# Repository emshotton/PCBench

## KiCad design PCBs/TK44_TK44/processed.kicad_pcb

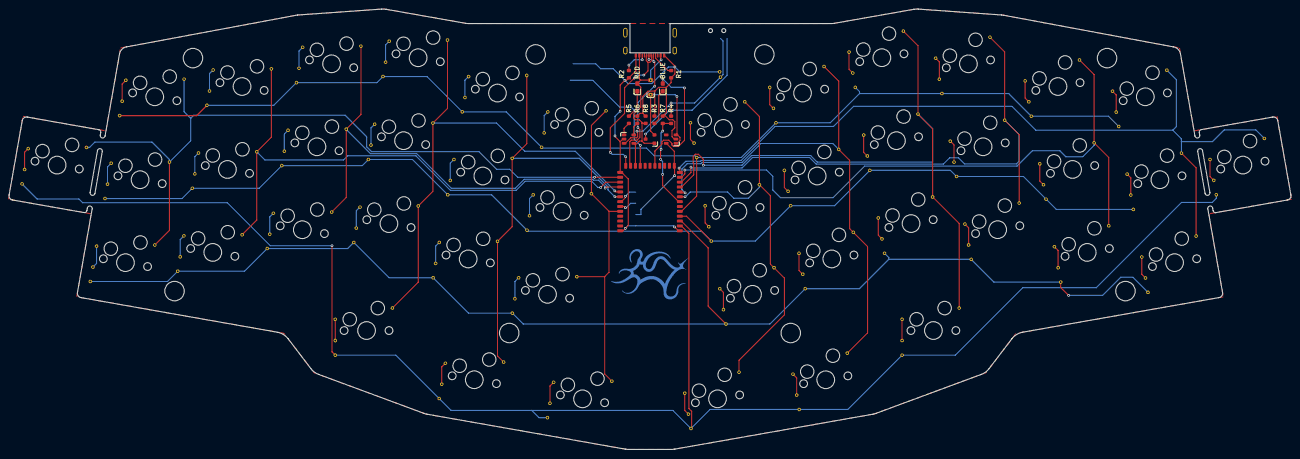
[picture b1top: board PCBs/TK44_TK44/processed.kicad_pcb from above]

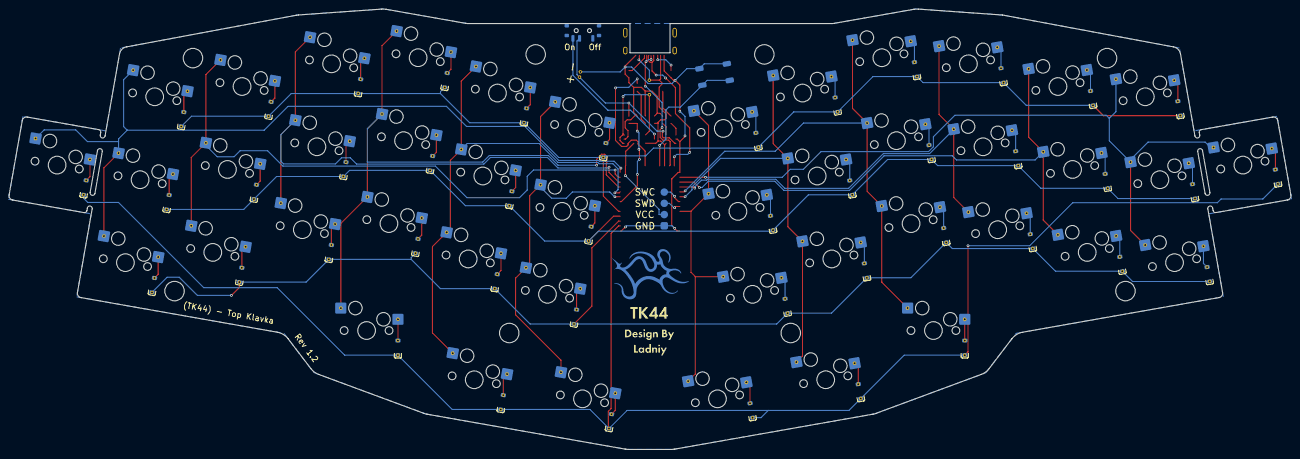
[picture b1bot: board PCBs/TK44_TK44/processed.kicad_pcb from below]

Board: 2 copper layers, 289.9 x 99.6 mm, 117 parts (48 on the bottom side), 79 nets.

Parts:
D1, D2, D3, D4, D5, D6, D7, D8, D9, D10, D11, D12, D13, D14, D15, D16, D17, D18, D19, D20, D21, D22, D23, D24, D25, D26, D27, D28, D29, D30, D31, D32, D33, D34, D35, D36, D37, D38, D39, D40, D41, D42, D43, D44, D46: 1N5819; D_SOD-123
D45: BLUE; LED_0603
D47: RED; LED_0603
H1, H2, H3, H4, H5, H6, H7, H8: Hole_Mount_M4
J1: BATT; Battery_Connector
J2: SWD; Connector_THT_1x4_2.54
J3: USB_C_Receptacle_USB2.0; USB-C-C168688
LOGO1: LOGO; logo
Q1: AO3407; SOT-23
R1, R2: 5.1K; R_0603
R3, R5: 1K; R_0603
R4: 810K; R_0603
R6: 3.3K; R_0603
R7: 2M; R_0603
R8: 100K; R_0603
SW1, SW2, SW3, SW4, SW5, SW6, SW7, SW8, SW9, SW10, SW11, SW12, SW13, SW14, SW15, SW16, SW17, SW18, SW19, SW20, SW21, SW22, SW23, SW24, SW25, SW26, SW27, SW28, SW29, SW30, SW31, SW32, SW33, SW34, SW35, SW36, SW37, SW39, SW42, SW44: MX; Switch_Mx_Hotswap_1u
SW38, SW40, SW41, SW43: MX; Switch_Mx_Hotswap_1.25u
SW45: SW_DPDT; MSK-12C02
SWT1: SW_Push; K2-1187SQ
U1: HOLYIOT-18010; Holyiot-18010-nRF52840
U2: MCP73831; SOT-23-5
U3: XC6220-3.3V; SOT-23-5

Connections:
/BLUE_LED: D45.2 (A), U1.18 (P0.23)
/BT_PIN: R4.2, R7.1, U1.7 (P0.02/AIN0)
/CC1: J3.A5 (CC1), R1.1
/CC2: J3.B5 (CC2), R2.1
/DATA+: J3.A6 (D+), J3.B6 (D+), U1.24 (USB_D+)
/DATA-: J3.A7 (D-), J3.B7 (D-), U1.23 (USB_D-)
/P0.04: SW11.2, SW23.2, SW35.2, U1.12 (P0.04/AIN2)
/P0.05: SW12.2, SW24.2, SW36.2, SW44.2, U1.13 (P0.05/AIN3)
/P0.22: SW1.2, SW13.2, SW25.2, SW37.2, U1.26 (P0.22)
/P0.28: SW7.2, SW19.2, SW31.2, SW41.2, U1.8 (P0.28/AIN4)
/P0.29: SW8.2, SW20.2, SW32.2, SW42.2, U1.9 (P0.29/AIN5)
/P0.30: SW9.2, SW21.2, SW33.2, SW43.2, U1.10 (P0.30/AIN6)
/P0.31: SW10.2, SW22.2, SW34.2, U1.11 (P0.31/AIN7)
/P1.00: SW2.2, SW14.2, SW26.2, U1.27 (P1.00)
/P1.01: SW4.2, SW16.2, SW28.2, SW38.2, U1.29 (P1.01)
/P1.02: SW5.2, SW17.2, SW29.2, SW39.2, U1.30 (P1.02)
/P1.03: SW3.2, SW15.2, SW27.2, U1.28 (P1.03)
/P1.04: SW6.2, SW18.2, SW30.2, SW40.2, U1.33 (P1.04)
/P1.10: D25.1 (K), D26.1 (K), D27.1 (K), D28.1 (K), D29.1 (K), D30.1 (K), D31.1 (K), D32.1 (K), D33.1 (K), D34.1 (K), D35.1 (K), D36.1 (K), U1.3 (P1.10)
/P1.11: D37.1 (K), D38.1 (K), D39.1 (K), D40.1 (K), D41.1 (K), D42.1 (K), D43.1 (K), D44.1 (K), U1.2 (P1.11)
/P1.13: D13.1 (K), D14.1 (K), D15.1 (K), D16.1 (K), D17.1 (K), D18.1 (K), D19.1 (K), D20.1 (K), D21.1 (K), D22.1 (K), D23.1 (K), D24.1 (K), U1.4 (P1.13)
/P1.15: D1.1 (K), D2.1 (K), D3.1 (K), D4.1 (K), D5.1 (K), D6.1 (K), D7.1 (K), D8.1 (K), D9.1 (K), D10.1 (K), D11.1 (K), D12.1 (K), U1.5 (P1.15)
/RESET: SWT1.1, U1.21 (P0.18/RESET)
/SWC: J2.4, U1.31 (SWDCLK)
/SWD: J2.3, U1.32 (SWDIO)
/VBAT: J1.1, R4.1, SW45.2, U2.3 (VBAT)
/VBUS: D46.2 (A), D47.2 (A), J3.A4 (VBUS), Q1.1 (G), R8.1, U1.22 (VBUS), U2.4 (VDD)
/nRF_VDD: J2.2, U1.14 (VDD), U3.5 (VOUT)
GND: J1.2, J2.1, J3.A1 (GND), R1.2, R2.2, R3.2, R6.2, R7.2, R8.2, SWT1.2, U1.1 (GND), U1.25 (GND), U1.37 (GND), U2.2 (VSS), U3.2 (GND)
unnamed: D1.2 (A), SW1.1
unnamed: D2.2 (A), SW2.1
unnamed: D3.2 (A), SW3.1
unnamed: D4.2 (A), SW4.1
unnamed: D5.2 (A), SW5.1
unnamed: D6.2 (A), SW6.1
unnamed: D7.2 (A), SW7.1
unnamed: D8.2 (A), SW8.1
unnamed: D9.2 (A), SW9.1
unnamed: D10.2 (A), SW10.1
unnamed: D11.2 (A), SW11.1
unnamed: D12.2 (A), SW12.1
unnamed: D13.2 (A), SW13.1
unnamed: D14.2 (A), SW14.1
unnamed: D15.2 (A), SW15.1
unnamed: D16.2 (A), SW16.1
unnamed: D17.2 (A), SW17.1
unnamed: D18.2 (A), SW18.1
unnamed: D19.2 (A), SW19.1
unnamed: D20.2 (A), SW20.1
unnamed: D21.2 (A), SW21.1
unnamed: D22.2 (A), SW22.1
unnamed: D23.2 (A), SW23.1
unnamed: D24.2 (A), SW24.1
unnamed: D25.2 (A), SW25.1
unnamed: D26.2 (A), SW26.1
unnamed: D27.2 (A), SW27.1
unnamed: D28.2 (A), SW28.1
unnamed: D29.2 (A), SW29.1
unnamed: D30.2 (A), SW30.1
unnamed: D31.2 (A), SW31.1
unnamed: D32.2 (A), SW32.1
unnamed: D33.2 (A), SW33.1
unnamed: D34.2 (A), SW34.1
unnamed: D35.2 (A), SW35.1
unnamed: D36.2 (A), SW36.1
unnamed: D37.2 (A), SW37.1
unnamed: D38.2 (A), SW38.1
unnamed: D39.2 (A), SW39.1
unnamed: D40.2 (A), SW40.1
unnamed: D41.2 (A), SW41.1
unnamed: D42.2 (A), SW42.1
unnamed: D43.2 (A), SW43.1
unnamed: D44.2 (A), SW44.1
unnamed: D45.1 (K), R3.1
unnamed: D46.1 (K), Q1.2 (S), U3.1 (VIN), U3.3 (EN)
unnamed: D47.1 (K), R5.1
unnamed: Q1.3 (D), SW45.3
unnamed: R5.2, U2.1 (STAT)
unnamed: R6.1, U2.5 (PROG)

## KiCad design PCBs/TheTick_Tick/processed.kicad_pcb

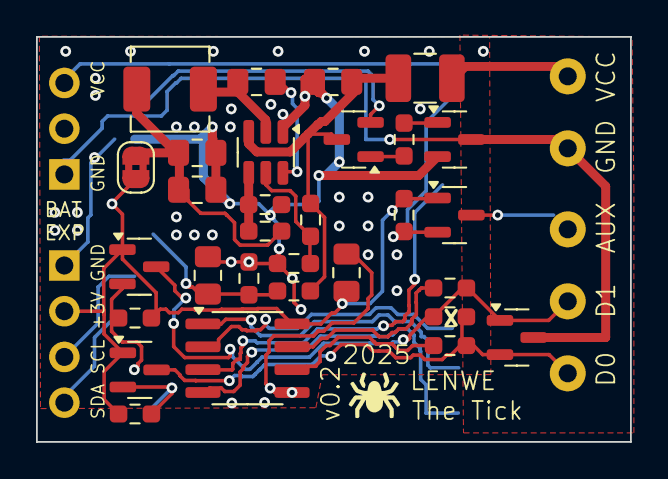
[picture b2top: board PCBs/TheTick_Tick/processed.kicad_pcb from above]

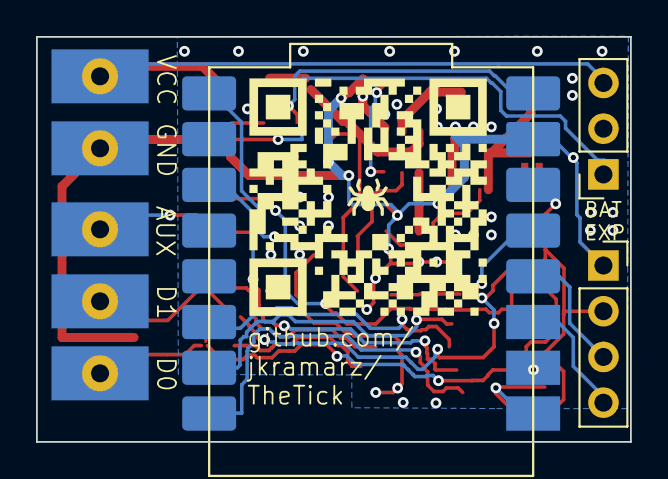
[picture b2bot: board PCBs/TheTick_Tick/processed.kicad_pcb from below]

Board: 2 copper layers, 33.0 x 22.5 mm, 35 parts (5 on the bottom side), 28 nets.

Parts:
C1, C2, C6: 100n; C_0805_2012Metric_Pad1.18x1.45mm_HandSolder
C3, C4, C5: 22u; C_0805_2012Metric_Pad1.18x1.45mm_HandSolder
D2: NUP2105L; SOT-23
D5: BAT54C; SOT-23
F1: 250mA 30V; Fuse_1210_3225Metric_Pad1.42x2.65mm_HandSolder
J1: Conn_01x03; KYOCERA 009176003022006 PTH
J2: Conn_01x02; KYOCERA 009176002022006 PTH
J3: Conn_01x04; PinSocket_1x04_P2.54mm_Vertical
J4: Conn_01x03; PinSocket_1x03_P2.54mm_Vertical
JP7: SolderJumper_2_Bridged; SolderJumper-2_P1.3mm_Bridged2Bar_RoundedPad1.0x1.5mm
L1: 10uH; L_Changjiang_FXL0420
Q1, Q2, Q3, Q4: 2N7002; SOT-23
R1, R8: 22k; R_0603_1608Metric_Pad0.98x0.95mm_HandSolder
R2, R10: 120k; R_0603_1608Metric_Pad0.98x0.95mm_HandSolder
R3, R4, R5, R6, R9: 12k; R_0603_1608Metric_Pad0.98x0.95mm_HandSolder
R7: 100k; R_0603_1608Metric_Pad0.98x0.95mm_HandSolder
R11, R12: 10; R_0603_1608Metric_Pad0.98x0.95mm_HandSolder
R13: 120; R_0603_1608Metric_Pad0.98x0.95mm_HandSolder
U1: TPS54202DDC; SOT-23-6
U2: THVD1410D; SOIC-8_3.9x4.9mm_P1.27mm
U3: ESP32-C3_SUPERMINI; MODULE_ESP32-C3_SUPERMINI_SMD

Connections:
+3.3V: C6.1, J3.2, JP7.2 (B), Q2.1 (G), Q3.1 (G), Q4.1 (G), R4.1, R6.1, R9.1, U2.8 (VCC), U3.3.3 (3V3)
+5V: D5.2, U3.5V
AUX: J1.3, Q3.3 (D)
AUX SENSE: Q3.2 (S), R4.2, U3.5 (GPIO5)
D0: D2.2 (K), J1.1, Q2.3 (D), R11.2, R13.2
D0 SENSE: Q2.2 (S), R9.2, U3.0 (GPIO0)
D1: D2.1 (K), J1.2, Q4.3 (D), R12.2, R13.1
D1 SENSE: Q4.2 (S), R6.2, U3.1 (GPIO1)
GND: C1.2, C3.2, C4.2, C5.2, C6.2, J3.1, Q1.2 (S), R1.2, R3.2, R8.1, U1.1 (GND), U2.5 (GND), U3.G (GND)
GNDPWR: D2.3 (A), J2.1, J4.1, Q1.3 (D)
LCD SCL: J3.3, U3.3 (GPIO3)
LCD SDA: J3.4, U3.2 (GPIO2)
unnamed: D5.1, R5.1
unnamed: C3.1, C4.1, JP7.1 (A), L1.1, R7.1
unnamed: Q1.1 (G), R5.2
unnamed: C2.1, U1.6 (BOOT)
unnamed: R2.1, R8.2, U1.5 (EN)
unnamed: R1.1, R7.2, U1.4 (FB)
unnamed: C2.2, L1.2, U1.2 (SW)
unnamed: C5.1, D5.3, F1.2, R2.2, R10.1, U1.3 (VIN)
unnamed: R11.1, U2.6 (A)
unnamed: R12.1, U2.7 (B)
RS485_DE: U2.3 (DE), U3.7 (GPIO7)
RS485_RE: U2.2 (~RE), U3.10 (GPIO10)
RS485_RX: U2.1 (RO), U3.20 (GPIO20)
RS485_TX: U2.4 (DI), U3.21 (GPIO21)
VDC: F1.1, J2.2, J4.3
V_SENSE: C1.1, R3.1, R10.2, U3.4 (GPIO4)

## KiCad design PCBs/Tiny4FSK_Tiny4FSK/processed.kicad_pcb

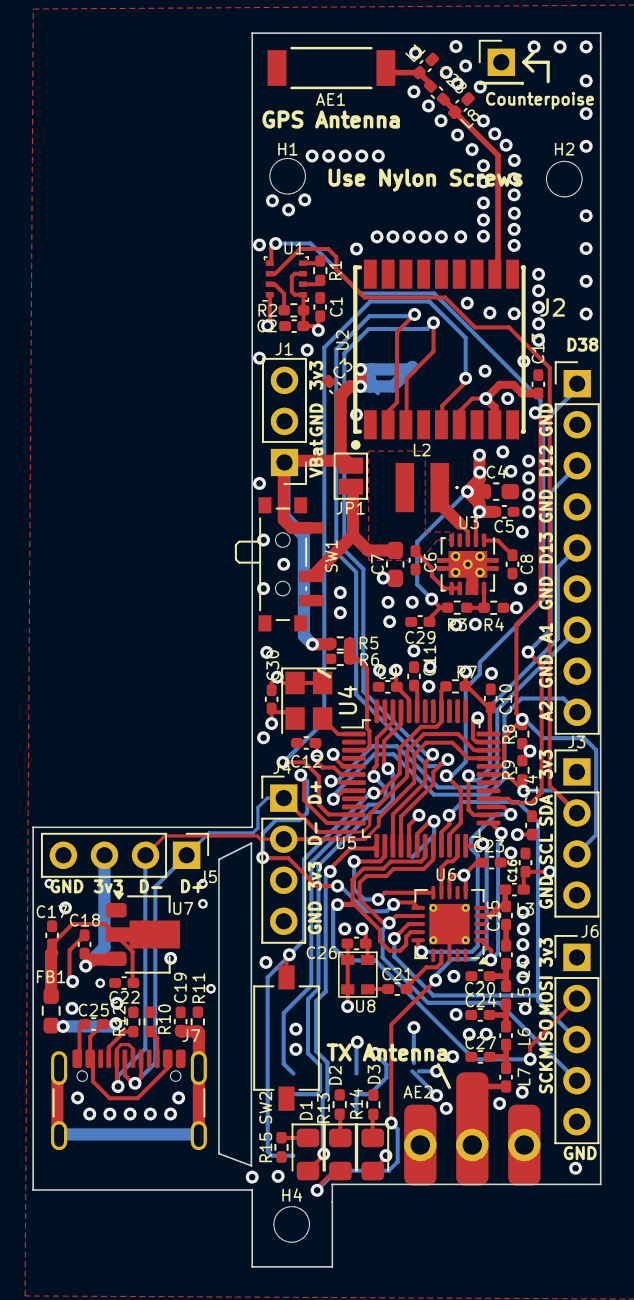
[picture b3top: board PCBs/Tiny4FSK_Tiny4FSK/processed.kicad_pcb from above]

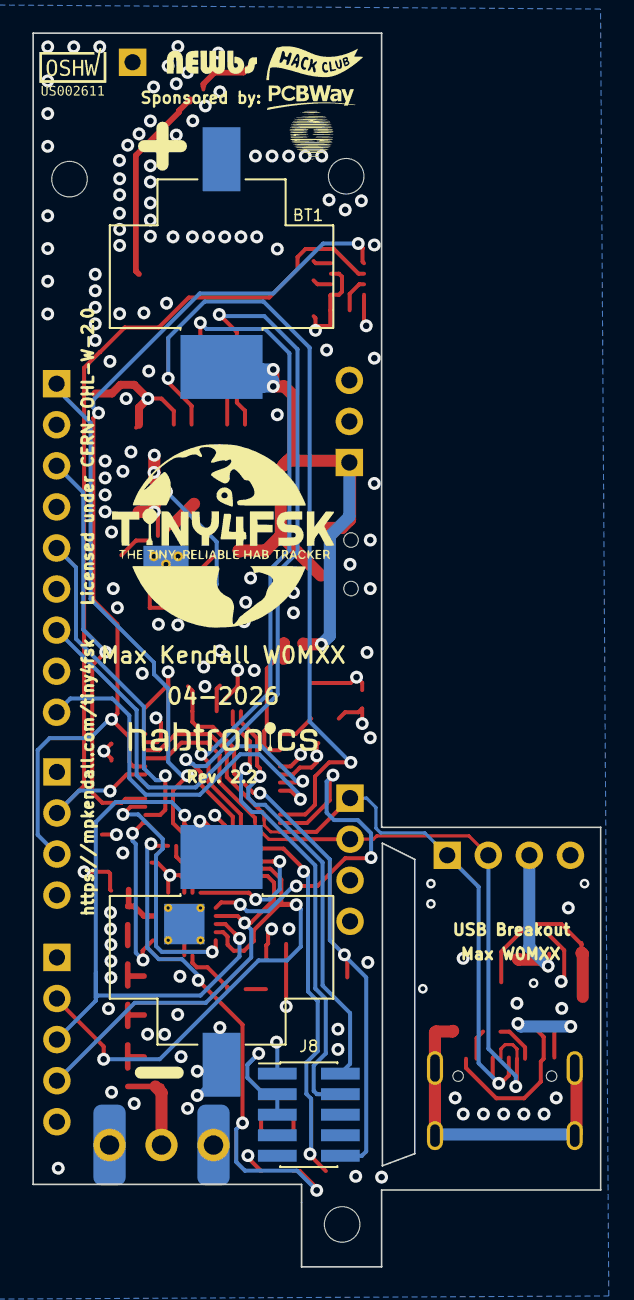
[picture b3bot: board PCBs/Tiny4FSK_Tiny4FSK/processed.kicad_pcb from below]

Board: 4 copper layers, 35.1 x 76.3 mm, 83 parts (2 on the bottom side), 55 nets.

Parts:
AE1: 1575AT43A0040; ANT_1575AT_JOT
AE2: TX Antenna; Antenna_Whip
BT1: BK-53; BAT_53
C1, C14: 10uF; C_0402_1005Metric_Pad0.74x0.62mm_HandSolder
C2, C3, C11, C18, C22: 1uF; C_0402_1005Metric_Pad0.74x0.62mm_HandSolder
C4: 22uF; C_0603_1608Metric_Pad1.08x0.95mm_HandSolder
C5, C8, C9, C13, C16, C23, C29: 100nF; C_0402_1005Metric_Pad0.74x0.62mm_HandSolder
C6, C10, C17, C25, C26, C30: 100 nF; C_0402_1005Metric_Pad0.74x0.62mm_HandSolder
C7: 10 uF; C_0603_1608Metric_Pad1.08x0.95mm_HandSolder
C12: 10 uF; C_0402_1005Metric_Pad0.74x0.62mm_HandSolder
C15: 9.1 pF; C_0402_1005Metric_Pad0.74x0.62mm_HandSolder
C19: 4.7 nF; C_0402_1005Metric_Pad0.74x0.62mm_HandSolder
C20: 8 pF; C_0402_1005Metric_Pad0.74x0.62mm_HandSolder
C21: 100 pF; C_0402_1005Metric_Pad0.74x0.62mm_HandSolder
C24: 6 pF; C_0402_1005Metric_Pad0.74x0.62mm_HandSolder
C27: 5 pF; C_0402_1005Metric_Pad0.74x0.62mm_HandSolder
C28: 2.7pF; C_0402_1005Metric_Pad0.74x0.62mm_HandSolder
D1: Success; LED_0805_2012Metric_Pad1.15x1.40mm_HandSolder
D2: Error; LED_0805_2012Metric_Pad1.15x1.40mm_HandSolder
D3: Power; LED_0805_2012Metric_Pad1.15x1.40mm_HandSolder
FB1: BLM18AG121SN1D; R_0603_1608Metric_Pad0.98x0.95mm_HandSolder
H1, H2, H4: MountingHole; MountingHole_2.2mm_M2
J1: Power Ext; PinHeader_1x03_P2.54mm_Vertical
J2: GPIO; PinHeader_1x09_P2.54mm_Vertical
J3: I2C; PinHeader_1x04_P2.54mm_Vertical
J4: USB; PinHeader_1x04_P2.54mm_Vertical
J5: USB Breakout; PinHeader_1x04_P2.54mm_Vertical
J6: SPI; PinHeader_1x05_P2.54mm_Vertical
J7: USBC; USB_C_Receptacle_GCT_USB4105-xx-A_16P_TopMnt_Horizontal
J8: SWD; PinHeader_2x05_P1.27mm_Vertical_SMD
J9: Counterpoise; PinHeader_1x01_P2.54mm_Vertical
JP1: Switch EN; SolderJumper-2_P1.3mm_Open_Pad1.0x1.5mm
L1, L8: 3.9 nH; L_0402_1005Metric_Pad0.77x0.64mm_HandSolder
L2: 2.2uH; LPS3015222MRB
L3: 220 nH; L_0402_1005Metric_Pad0.77x0.64mm_HandSolder
L4, L5, L6, L7: 14 nH; L_0402_1005Metric_Pad0.77x0.64mm_HandSolder
R1, R2: 10k; R_0402_1005Metric_Pad0.72x0.64mm_HandSolder
R3, R5, R6, R11: 1M; R_0402_1005Metric_Pad0.72x0.64mm_HandSolder
R4: 180k; R_0402_1005Metric_Pad0.72x0.64mm_HandSolder
R7: 220; R_0402_1005Metric_Pad0.72x0.64mm_HandSolder
R8, R9: 1.8k; R_0402_1005Metric_Pad0.72x0.64mm_HandSolder
R10, R12: 5k1; R_0402_1005Metric_Pad0.72x0.64mm_HandSolder
R13, R14, R15: 330; R_0402_1005Metric_Pad0.72x0.64mm_HandSolder
SW1: Power Switch; SW_SPDT_PCM12
SW2: RST; SW_Tactile_SPST_NO_Straight_CK_PTS636Sx25SMTRLFS
U1: BME280; Bosch_LGA-8_2.5x2.5mm_P0.65mm_ClockwisePinNumbering
U2: ATGM336H
U3: TPS61200DRC; Texas_S-PVSON-N10_ThermalVias
U4: ECS-327TXO-2012; Crystal_SMD_3225-4Pin_3.2x2.5mm
U5: ATSAMD21G18A-A; TQFP-48_7x7mm_P0.5mm
U6: SI4063; QFN-20-1EP_4x4mm_P0.5mm_EP2.5x2.5mm_ThermalVias
U7: Linear Step-Down; MCP1700
U8: ECS-TXO-20CSMV4

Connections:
+3.3V: C1.2, C2.1, C4.1, C5.1, C9.2, C10.1, C12.1, C13.2, C14.1, C16.2, C18.1, C23.1, C26.2, C29.1, C30.2, D3.2 (A), J1.3, J3.1, J4.3, J5.3, J6.1, J8.1, L3.1, R2.1, R3.1, R7.2, R8.1, R9.2, U1.6 (VDDIO), U1.8 (VDD), U2.6 (VBAT), U2.8 (VCC), U3.2 (VOUT), U4.1 (EN), U4.4 (VDD), U5.6 (VDDANA), U5.17 (VDDIO), U5.36 (VDDIO), U5.44 (VDDIN), U6.6 (VDD_1), U6.8 (VDD_2), U7.2 (VO), U8.4 (VDD)
+BATT: BT1.1 (+), C3.1, J1.1, JP1.2 (B), R5.1, SW1.1 (A)
A1: J2.7, U5.7 (PB08)
A2: J2.9, U5.8 (PB09)
ANT_GPS: C28.1, L8.2, U2.11 (RF_IN)
BATT_SENSE: R5.2, R6.1, U5.3 (PA02)
BST_IN: C6.1, C7.1, JP1.1 (A), L2.2, SW1.2 (B), U3.5 (VIN), U3.6 (EN), U3.7 (UVLO)
D12: J2.3, U5.28 (PA19)
D13: J2.5, U5.26 (PA17)
D38: J2.1, U5.22 (PA13)
D+: J4.1, J5.1, J7.A6 (D+), J7.B6 (D+), U5.34 (PA25)
D-: J4.2, J5.2, J7.A7 (D-), J7.B7 (D-), U5.33 (PA24)
ERROR: D2.2 (A), U5.24 (PA15)
Earth: AE2.2 (Shield), BT1.2 (-), C1.1, C2.2, C3.2, C4.2, C5.2, C6.2, C7.2, C8.2, C9.1, C10.2, C11.2, C12.2, C13.1, C14.2, C16.1, C17.2, C18.2, C19.1, C20.2, C22.1, C23.2, C24.2, C25.2, C26.1, C27.2, C29.2, C30.1, J1.2, J2.2, J2.4, J2.6, J2.8, J3.4, J4.4, J5.4, J6.5, J7.A1 (GND), J7.A12 (GND), J7.B1 (GND), J7.B12 (GND), J8.3, J8.5, J9.1 (Pin_1_1), L1.1, L8.1, R1.2, R4.2, R6.2, R10.1, R11.2, R12.1, R13.2, R14.2, R15.2, SW2.1, U1.1 (GND), U1.7 (GND), U2.1 (GND), U2.10 (GND), U2.12 (GND), U3.4 (PGND), U3.8 (PS), U3.9 (GND), U3.11 (PAD), U4.2 (GND), U5.5 (GNDANA), U5.18 (GND), U5.35 (GND), U5.42 (GND), U6.18 (GND_1), U6.21 (GND_2), U7.1 (GND), U8.1 (GND), U8.2 (GND)
GPIO0: U5.23 (PA14), U6.9 (GPIO0)
GPIO1: U5.14 (PA09), U6.10 (GPIO1)
GPS_EN: U2.5 (ONOFF), U5.11 (PA06)
LIN: C17.1, C22.2, FB1.2, U7.3 (VI)
MISO: J6.3, U5.21 (PA12), U6.13 (SDO)
MOSI: J6.2, U5.19 (PB10), U6.14 (SDI)
unnamed: AE1.1 (A_1), C28.2, L1.2
unnamed: AE2.1 (RF), L7.2
unnamed: C15.2, L4.1
unnamed: C20.1, L4.2, L5.1
unnamed: C24.1, L5.2, L6.1
unnamed: C27.1, L6.2, L7.1
unnamed: D1.1 (K), R15.1
unnamed: D2.1 (K), R13.1
unnamed: D3.1 (K), R14.1
unnamed: J7.A5 (CC1), R12.2
unnamed: J7.B5 (CC2), R10.2
unnamed: C19.2, J7.S1 (SHIELD), R11.1
unnamed: R2.2, U1.2 (CSB)
unnamed: R1.1, U1.5 (SDO)
unnamed: R3.2, R4.1, U3.10 (FB)
unnamed: L2.1, U3.3 (L)
unnamed: C8.1, U3.1 (VAUX)
unnamed: C11.1, U5.43 (VDDCORE)
unnamed: C21.2, U6.17 (XIN)
RF_ANT: C15.1, L3.2, U6.4 (TX)
RF_RST: U5.12 (PA07), U6.11 (NIRQ)
RF_SS: U5.27 (PA18), U6.15 (NSEL)
RF_XO: C21.1, U8.3 (CLK_OUT)
RXD: U2.2 (TXD), U5.16 (PA11)
SCK: J6.4, U5.20 (PB11), U6.12 (SCLK)
SCL: J3.3, R8.2, U1.4 (SCK), U5.32 (PA23)
SDA: J3.2, R9.1, U1.3 (SDI), U5.31 (PA22)
SDN: U5.25 (PA16), U6.1 (SDN)
SUCCESS: D1.2 (A), U5.13 (PA08)
SWCLK: J8.4, U5.45 (PA30)
SWDIO: J8.2, U5.46 (PA31)
TCXO: U4.3 (OUTPUT), U5.1 (PA00)
TXD: U2.3 (RXD), U5.15 (PA10)
USB: C25.1, FB1.1, J7.A4 (VBUS), J7.A9 (VBUS), J7.B4 (VBUS), J7.B9 (VBUS)
nRST: J8.10, R7.1, SW2.2, U5.40 (~RESET)

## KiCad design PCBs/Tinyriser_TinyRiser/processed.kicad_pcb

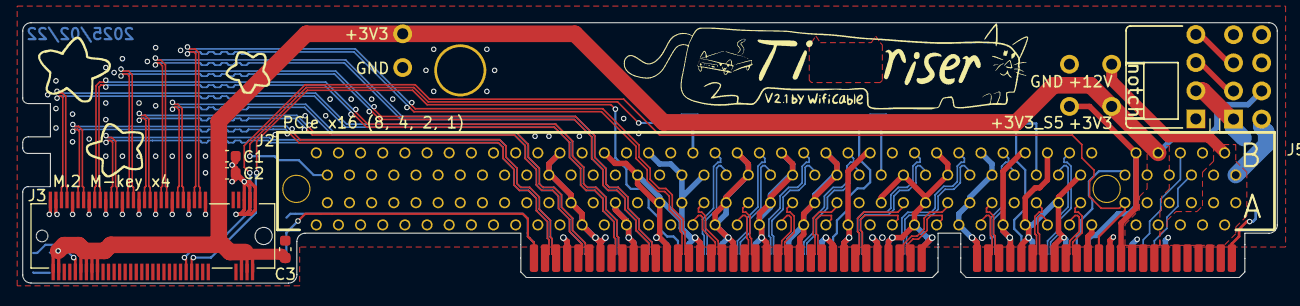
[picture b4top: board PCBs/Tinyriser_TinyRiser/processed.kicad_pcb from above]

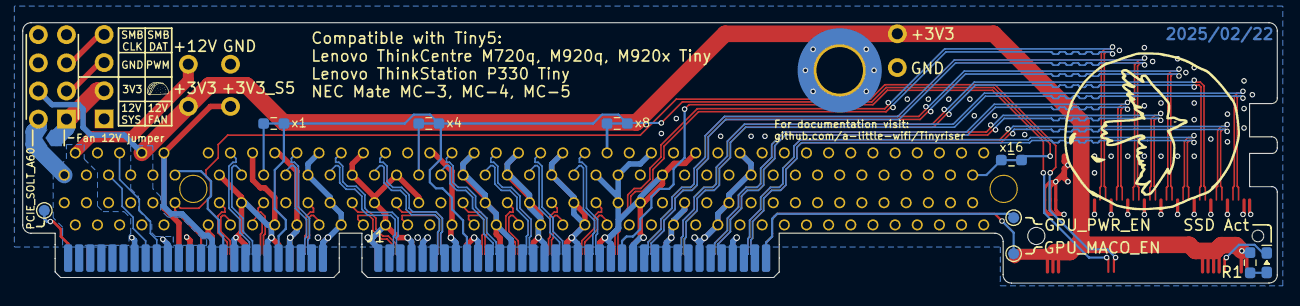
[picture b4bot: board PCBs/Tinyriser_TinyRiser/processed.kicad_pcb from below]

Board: 4 copper layers, 113.2 x 23.5 mm, 25 parts (12 on the bottom side), 70 nets.

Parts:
C1, C3: 10uF; C_0603_1608Metric
C2: 100nF; C_0603_1608Metric
D1: LED; D_0603_1608Metric_Pad1.05x0.95mm_HandSolder
H1: MountingHole_Pad; MountingHole_4.3mm_M4_ISO7380_Pad_TopOnly
J1: TinyRiser
J2: Bus_PCI_Express_x16; PCIe_x16_tht
J3: Bus_M.2_Socket_M; M.2_NGFF_KeyM_H5.3_Vertical
J5: Conn_02x04_Odd_Even; PinSocket_2x04_P2.54mm_Horizontal
JP1: SolderJumper_2_Open; SolderJumper-2_P1.3mm_Open_TrianglePad1.0x1.5mm
M1: Fan_4pin; PinHeader_1x04_P2.54mm_Horizontal
R1: 5K1; R_0603_1608Metric_Pad0.98x0.95mm_HandSolder
R3, R4, R5, R6: 0R; R_0603_1608Metric_Pad0.98x0.95mm_HandSolder
TP1: PCIE_SOLT_A60; TestPoint_Pad_D1.0mm
TP2: GPU_MACO_EN; TestPoint_Pad_D1.0mm
TP3: GPU_PWR_EN; TestPoint_Pad_D1.0mm
TP4, TP8: +3V3; TestPoint_THTPad_D1.5mm_Drill0.7mm
TP5: +3V3_S5; TestPoint_THTPad_D1.5mm_Drill0.7mm
TP6, TP7: GND; TestPoint_THTPad_D1.5mm_Drill0.7mm
TP9: +12V; TestPoint_THTPad_D1.5mm_Drill0.7mm

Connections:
+3V3: C1.1, C2.1, C3.1, J1.A51 (+3V3), J1.A52 (+3V3), J1.A53 (+3V3), J1.B48 (+3V3), J1.B49 (+3V3), J1.B50 (+3V3), J2.A9 (+3.3V), J2.A10 (+3.3V), J2.B8 (+3.3V), J3.2 (3.3V), J3.4 (3.3V), J3.12 (3.3V), J3.14 (3.3V), J3.16 (3.3V), J3.18 (3.3V), J3.70 (3.3V), J3.72 (3.3V), J3.74 (3.3V), J5.4, R1.2, TP4.1, TP8.1
+3V3_S5: J1.A50 (+3V3_S5), J1.B47 (+3V3_S5), J2.B10 (3.3Vaux), TP5.1
+12V: J1.A54 (+12V), J1.A55 (+12V), J1.A56 (+12V), J1.A57 (+12V), J1.A58 (+12V), J1.A59 (+12V), J1.B55 (+12V), J1.B56 (+12V), J1.B57 (+12V), J1.B58 (+12V), J1.B59 (+12V), J1.B60 (+12V), J2.A2 (+12V), J2.A3 (+12V), J2.B1 (+12V), J2.B2 (+12V), J2.B3 (+12V), J5.2, JP1.2 (B), TP9.1
+12V_fan: J5.1, JP1.1 (A), M1.2 (+)
GND: C1.2, C2.2, C3.2, H1.1, J1.A4 (GND), J1.A7 (GND), J1.A10 (GND), J1.A13 (GND), J1.A16 (GND), J1.A19 (GND), J1.A22 (GND), J1.A25 (GND), J1.A28 (GND), J1.A29 (GND), J1.A32 (GND), J1.A33 (GND), J1.A36 (GND), J1.A37 (GND), J1.A40 (GND), J1.A41 (GND), J1.A44 (GND), J1.A47 (GND), J1.A49 (GND), J1.B4 (GND), J1.B7 (GND), J1.B10 (GND), J1.B13 (GND), J1.B15 (GND), J1.B18 (GND), J1.B21 (GND), J1.B24 (GND), J1.B27 (GND), J1.B29 (GND), J1.B32 (GND), J1.B33 (GND), J1.B36 (GND), J1.B37 (GND), J1.B40 (GND), J1.B42 (GND), J1.B45 (GND), J1.B51 (GND), J1.B54 (GND), J2.A1 (~PRSNT1), J2.A4 (GND), J2.A12 (GND), J2.A15 (GND), J2.A18 (GND), J2.A20 (GND), J2.A23 (GND), J2.A24 (GND), J2.A27 (GND), J2.A28 (GND), J2.A31 (GND), J2.A34 (GND), J2.A37 (GND), J2.A38 (GND), J2.A41 (GND), J2.A42 (GND), J2.A45 (GND), J2.A46 (GND), J2.A49 (GND), J2.A51 (GND), J2.A54 (GND), J2.A55 (GND), J2.A58 (GND), J2.A59 (GND), J2.A62 (GND), J2.A63 (GND), J2.A66 (GND), J2.A67 (GND), J2.A70 (GND), J2.A71 (GND), J2.A74 (GND), J2.A75 (GND), J2.A78 (GND), J2.A79 (GND), J2.A82 (GND), J2.B4 (GND), J2.B7 (GND), J2.B13 (GND), J2.B16 (GND), J2.B18 (GND), J2.B21 (GND), J2.B22 (GND), J2.B25 (GND), J2.B26 (GND), J2.B29 (GND), J2.B32 (GND), J2.B35 (GND), J2.B36 (GND), J2.B39 (GND), J2.B40 (GND), J2.B43 (GND), J2.B44 (GND), J2.B47 (GND), J2.B49 (GND), J2.B52 (GND), J2.B53 (GND), J2.B56 (GND), J2.B57 (GND), J2.B60 (GND), J2.B61 (GND), J2.B64 (GND), J2.B65 (GND), J2.B68 (GND), J2.B69 (GND), J2.B72 (GND), J2.B73 (GND), J2.B76 (GND), J2.B77 (GND), J2.B80 (GND), J3.1 (GND), J3.3 (GND), J3.9 (GND), J3.15 (GND), J3.21 (GND), J3.27 (GND), J3.33 (GND), J3.39 (GND), J3.45 (GND), J3.51 (GND), J3.57 (GND), J3.71 (GND), J3.73 (GND), J3.75 (GND), J5.6, M1.1 (-), TP6.1, TP7.1
unnamed: D1.2 (A), R1.1
unnamed: D1.1 (K), J3.10 (DAS/~DSS/~LED1)
unnamed: J1.A1 (GPU_MACO_EN), TP2.1
unnamed: J1.B1 (GPU_PWR_EN), TP3.1
unnamed: J1.A60 (PCIE_SOLT_A60), TP1.1
PCIe_CPU_CLKREQ#: J1.B28 (PCIe_CPU_CLKREQ#), J1.B41 (PCIe_CPU_CLKREQ#), J2.B17 (~PRSNT2), J2.B31 (~PRSNT2), J2.B48 (~PRSNT2), J2.B81 (~PRSNT2), R3.1, R3.2, R4.1, R4.2, R5.1, R5.2, R6.1, R6.2
PCIe_CPU_REFCLK+: J1.A46 (PCIe_CPU_REFCLK+), J2.A13 (REFCLK+)
PCIe_CPU_REFCLK-: J1.A45 (PCIe_CPU_REFCLK-), J2.A14 (REFCLK-)
PCIe_CPU_Rx0+: J1.A43 (PCIe_CPU_Rx0+), J2.A16 (PERp0)
PCIe_CPU_Rx0-: J1.A42 (PCIe_CPU_Rx0-), J2.A17 (PERn0)
PCIe_CPU_Rx1+: J1.A39 (PCIe_CPU_Rx1+), J2.A21 (PERp1)
PCIe_CPU_Rx1-: J1.A38 (PCIe_CPU_Rx1-), J2.A22 (PERn1)
PCIe_CPU_Rx2+: J1.A34 (PCIe_CPU_Rx2+), J2.A25 (PERp2)
PCIe_CPU_Rx2-: J1.A35 (PCIe_CPU_Rx2-), J2.A26 (PERn2)
PCIe_CPU_Rx3+: J1.A30 (PCIe_CPU_Rx3+), J2.A29 (PERp3)
PCIe_CPU_Rx3-: J1.A31 (PCIe_CPU_Rx3-), J2.A30 (PERn3)
PCIe_CPU_Rx4+: J1.A26 (PCIe_CPU_Rx4+), J2.A35 (PERp4)
PCIe_CPU_Rx4-: J1.A27 (PCIe_CPU_Rx4-), J2.A36 (PERn4)
PCIe_CPU_Rx5+: J1.A24 (PCIe_CPU_Rx5+), J2.A39 (PERp5)
PCIe_CPU_Rx5-: J1.A23 (PCIe_CPU_Rx5-), J2.A40 (PERn5)
PCIe_CPU_Rx6+: J1.A21 (PCIe_CPU_Rx6+), J2.A43 (PERp6)
PCIe_CPU_Rx6-: J1.A20 (PCIe_CPU_Rx6-), J2.A44 (PERn6)
PCIe_CPU_Rx7+: J1.A18 (PCIe_CPU_Rx7+), J2.A47 (PERp7)
PCIe_CPU_Rx7-: J1.A17 (PCIe_CPU_Rx7-), J2.A48 (PERn7)
PCIe_CPU_Tx0+: J1.B44 (PCIe_CPU_Tx0+), J2.B14 (PETp0)
PCIe_CPU_Tx0-: J1.B43 (PCIe_CPU_Tx0-), J2.B15 (PETn0)
PCIe_CPU_Tx1+: J1.B39 (PCIe_CPU_Tx1+), J2.B19 (PETp1)
PCIe_CPU_Tx1-: J1.B38 (PCIe_CPU_Tx1-), J2.B20 (PETn1)
PCIe_CPU_Tx2+: J1.B35 (PCIe_CPU_Tx2+), J2.B23 (PETp2)
PCIe_CPU_Tx2-: J1.B34 (PCIe_CPU_Tx2-), J2.B24 (PETn2)
PCIe_CPU_Tx3+: J1.B31 (PCIe_CPU_Tx3+), J2.B27 (PETp3)
PCIe_CPU_Tx3-: J1.B30 (PCIe_CPU_Tx3-), J2.B28 (PETn3)
PCIe_CPU_Tx4+: J1.B26 (PCIe_CPU_Tx4+), J2.B33 (PETp4)
PCIe_CPU_Tx4-: J1.B25 (PCIe_CPU_Tx4-), J2.B34 (PETn4)
PCIe_CPU_Tx5+: J1.B23 (PCIe_CPU_Tx5+), J2.B37 (PETp5)
PCIe_CPU_Tx5-: J1.B22 (PCIe_CPU_Tx5-), J2.B38 (PETn5)
PCIe_CPU_Tx6+: J1.B20 (PCIe_CPU_Tx6+), J2.B41 (PETp6)
PCIe_CPU_Tx6-: J1.B19 (PCIe_CPU_Tx6-), J2.B42 (PETn6)
PCIe_CPU_Tx7+: J1.B17 (PCIe_CPU_Tx7+), J2.B45 (PETp7)
PCIe_CPU_Tx7-: J1.B16 (PCIe_CPU_Tx7-), J2.B46 (PETn7)
PCIe_PCH_CLKREQ#: J1.B14 (PCIe_PCH_CLKREQ#), J3.52 (~CLKREQ)
PCIe_PCH_REFCLK+: J1.A15 (PCIe_PCH_REFCLK+), J3.55 (REFCLKp)
PCIe_PCH_REFCLK-: J1.A14 (PCIe_PCH_REFCLK-), J3.53 (REFCLKn)
PCIe_PCH_Rx0+: J1.B12 (PCIe_PCH_Rx0+), J3.43 (PERp0/SATA-B-)
PCIe_PCH_Rx0-: J1.B11 (PCIe_PCH_Rx0-), J3.41 (PERn0/SATA-B+)
PCIe_PCH_Rx1+: J1.A12 (PCIe_PCH_Rx1+), J3.31 (PERp1)
PCIe_PCH_Rx1-: J1.A11 (PCIe_PCH_Rx1-), J3.29 (PERn1)
PCIe_PCH_Rx2+: J1.A8 (PCIe_PCH_Rx2+), J3.19 (PERp2)
PCIe_PCH_Rx2-: J1.A9 (PCIe_PCH_Rx2-), J3.17 (PERn2)
PCIe_PCH_Rx3+: J1.B9 (PCIe_PCH_Rx3+), J3.7 (PERp3)
PCIe_PCH_Rx3-: J1.B8 (PCIe_PCH_Rx3-), J3.5 (PERn3)
PCIe_PCH_Tx0+: J1.B6 (PCIe_PCH_Tx0+), J3.49 (PETp0/SATA-A+)
PCIe_PCH_Tx0-: J1.B5 (PCIe_PCH_Tx0-), J3.47 (PETn0/SATA-A-)
PCIe_PCH_Tx1+: J1.A6 (PCIe_PCH_Tx1+), J3.37 (PETp1)
PCIe_PCH_Tx1-: J1.A5 (PCIe_PCH_Tx1-), J3.35 (PETn1)
PCIe_PCH_Tx2+: J1.B3 (PCIe_PCH_Tx2+), J3.25 (PETp2)
PCIe_PCH_Tx2-: J1.B2 (PCIe_PCH_Tx2-), J3.23 (PETn2)
PCIe_PCH_Tx3+: J1.A3 (PCIe_PCH_Tx3+), J3.13 (PETp3)
PCIe_PCH_Tx3-: J1.A2 (PCIe_PCH_Tx3-), J3.11 (PETn3)
PERST#: J1.A48 (PCIe_RST#), J2.A11 (~PERST), J3.50 (~PERST)
PWM_fan: J5.5, M1.4 (PWM)
SMBCLK: J1.B53 (SMBCLK), J2.B5 (SMCLK), J5.8
SMBDATA: J1.B52 (SMBDATA), J2.B6 (SMDAT), J5.7
Taco_fan: J5.3, M1.3 (Tacho)
WAKE#: J1.B46 (WAKE#), J2.B11 (~WAKE)

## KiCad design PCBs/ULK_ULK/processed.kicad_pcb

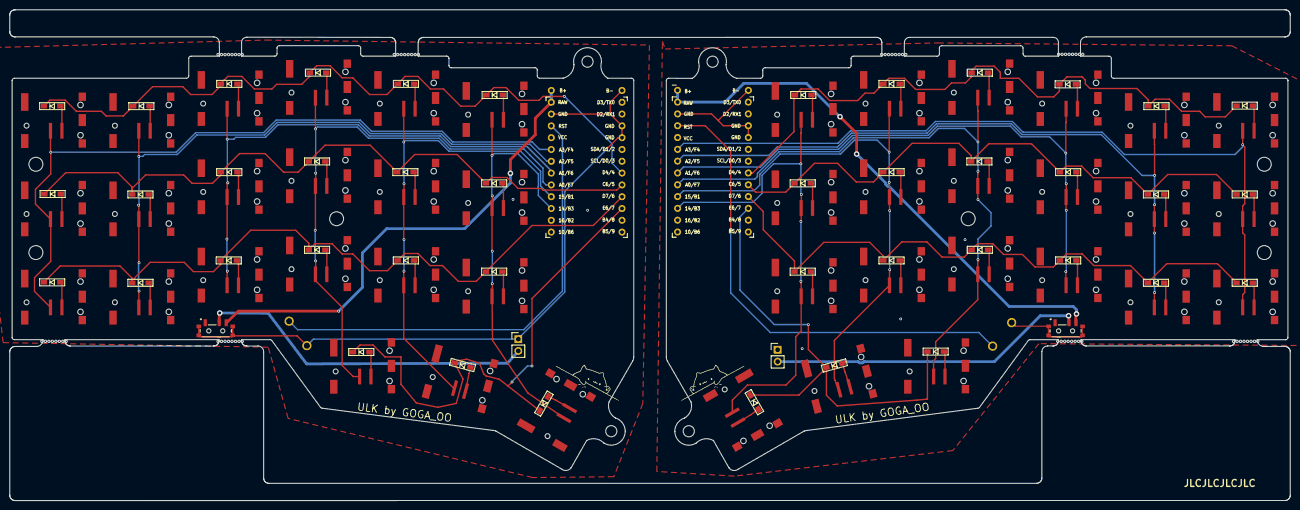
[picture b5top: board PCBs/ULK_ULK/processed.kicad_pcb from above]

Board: 2 copper layers, 275.5 x 105.6 mm, 100 parts (0 on the bottom side), 70 nets.

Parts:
D1, D2, D3, D4, D5, D6, D7, D8, D9, D10, D11, D12, D13, D14, D15, D16, D17, D18, D19, D20, D21, D22, D23, D24, D25, D26, D27, D28, D29, D30, D31, D32, D33, D34, D35, D36, D37, D38, D39, D40, D41, D42: D; D3_SMD_v2
RSW1, RSW2: SW_RESET; ResetSW_1side
SW1, SW2, SW3, SW4, SW5, SW6, SW7, SW8, SW9, SW10, SW11, SW12, SW13, SW14, SW15, SW16, SW17, SW18, SW19, SW20, SW21, SW22, SW23, SW24, SW25, SW26, SW27, SW28, SW29, SW30, SW31, SW32, SW33, SW34, SW35, SW36, SW37, SW38, SW39, SW40, SW41, SW42: SW_PUSH; Cherry_ULP_SMD
SW43, SW44: PCM12SMTR; SW_PCM12SMTR
U1, U2: ProMicro; ProMicro_v3
U3, U5: PinHeader_1x02_P2.54mm_Vertical
mouse-bite-2mm-slot, mouse-bite-2mm-slot#2, mouse-bite-2mm-slot#3, mouse-bite-2mm-slot#4, mouse-bite-2mm-slot#5, mouse-bite-2mm-slot#6, mouse-bite-2mm-slot#7, mouse-bite-2mm-slot#8: VAL**; mouse-bite-2mm-slot

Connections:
1V5: SW44.3, U2.24 (RAW)
+1V5: SW43.3, U1.24 (RAW)
GND: RSW1.2, SW1.3 (G), SW2.3 (G), SW3.3 (G), SW4.3 (G), SW5.3 (G), SW6.3 (G), SW7.3 (G), SW8.3 (G), SW9.3 (G), SW10.3 (G), SW11.3 (G), SW12.3 (G), SW13.3 (G), SW14.3 (G), SW15.3 (G), SW16.3 (G), SW17.3 (G), SW18.3 (G), SW19.3 (G), SW20.3 (G), SW21.3 (G), SW43.S1 (SHIELD), SW43.S2 (SHIELD), SW43.S3 (SHIELD), SW43.S4 (SHIELD), U1.3 (GND), U1.4 (GND), U1.23 (GND), U3.1 (-)
GNDA: RSW2.2, SW22.3 (G), SW23.3 (G), SW24.3 (G), SW25.3 (G), SW26.3 (G), SW27.3 (G), SW28.3 (G), SW29.3 (G), SW30.3 (G), SW31.3 (G), SW32.3 (G), SW33.3 (G), SW34.3 (G), SW35.3 (G), SW36.3 (G), SW37.3 (G), SW38.3 (G), SW39.3 (G), SW40.3 (G), SW41.3 (G), SW42.3 (G), SW44.S1 (SHIELD), SW44.S2 (SHIELD), SW44.S3 (SHIELD), SW44.S4 (SHIELD), U2.3 (GND), U2.4 (GND), U2.23 (GND), U5.1 (-)
unnamed: D1.2 (A), SW1.2
unnamed: D2.2 (A), SW2.2
unnamed: D3.2 (A), SW3.2
unnamed: D4.2 (A), SW4.2
unnamed: D5.2 (A), SW5.2
unnamed: D6.2 (A), SW6.2
unnamed: D7.2 (A), SW7.2
unnamed: D8.2 (A), SW8.2
unnamed: D9.2 (A), SW9.2
unnamed: D10.2 (A), SW10.2
unnamed: D11.2 (A), SW11.2
unnamed: D12.2 (A), SW12.2
unnamed: D13.2 (A), SW13.2
unnamed: D14.2 (A), SW14.2
unnamed: D15.2 (A), SW15.2
unnamed: D16.2 (A), SW16.2
unnamed: D17.2 (A), SW17.2
unnamed: D18.2 (A), SW18.2
unnamed: D19.2 (A), SW19.2
unnamed: D20.2 (A), SW20.2
unnamed: D21.2 (A), SW21.2
unnamed: D22.2 (A), SW22.2
unnamed: D23.2 (A), SW23.2
unnamed: D24.2 (A), SW24.2
unnamed: D25.2 (A), SW25.2
unnamed: D26.2 (A), SW26.2
unnamed: D27.2 (A), SW27.2
unnamed: D28.2 (A), SW28.2
unnamed: D29.2 (A), SW29.2
unnamed: D30.2 (A), SW30.2
unnamed: D31.2 (A), SW31.2
unnamed: D32.2 (A), SW32.2
unnamed: D33.2 (A), SW33.2
unnamed: D34.2 (A), SW34.2
unnamed: D35.2 (A), SW35.2
unnamed: D36.2 (A), SW36.2
unnamed: D37.2 (A), SW37.2
unnamed: D38.2 (A), SW38.2
unnamed: D39.2 (A), SW39.2
unnamed: D40.2 (A), SW40.2
unnamed: D41.2 (A), SW41.2
unnamed: D42.2 (A), SW42.2
unnamed: SW43.2, U3.2 (+)
unnamed: SW44.2, U5.2 (+)
col0: SW1.1, SW7.1, SW13.1, U1.20 (F4/A3)
col0_r: SW22.1, SW28.1, SW34.1, U2.20 (F4/A3)
col1: SW2.1, SW8.1, SW14.1, U1.19 (F5/A2)
col1_r: SW23.1, SW29.1, SW35.1, U2.19 (F5/A2)
col2: SW3.1, SW9.1, SW15.1, U1.18 (F6/A1)
col2_r: SW24.1, SW30.1, SW36.1, U2.18 (F6/A1)
col3: SW4.1, SW10.1, SW16.1, SW19.1, U1.17 (F7/A0)
col3_r: SW25.1, SW31.1, SW37.1, SW40.1, U2.17 (F7/A0)
col4: SW5.1, SW11.1, SW17.1, SW20.1, U1.16 (B1/15)
col4_r: SW26.1, SW32.1, SW38.1, SW41.1, U2.16 (B1/15)
col5: SW6.1, SW12.1, SW18.1, SW21.1, U1.15 (B3/14)
col5_r: SW27.1, SW33.1, SW39.1, SW42.1, U2.15 (B3/14)
reset: RSW1.1, U1.22 (RST)
reset_r: RSW2.1, U2.22 (RST)
row0: D1.1 (K), D2.1 (K), D3.1 (K), D4.1 (K), D5.1 (K), D6.1 (K), U1.7 (4/D4)
row0_r: D22.1 (K), D23.1 (K), D24.1 (K), D25.1 (K), D26.1 (K), D27.1 (K), U2.7 (4/D4)
row1: D7.1 (K), D8.1 (K), D9.1 (K), D10.1 (K), D11.1 (K), D12.1 (K), U1.8 (5/C6)
row1_r: D28.1 (K), D29.1 (K), D30.1 (K), D31.1 (K), D32.1 (K), D33.1 (K), U2.8 (5/C6)
row2: D13.1 (K), D14.1 (K), D15.1 (K), D16.1 (K), D17.1 (K), D18.1 (K), U1.9 (6/D7)
row2_r: D34.1 (K), D35.1 (K), D36.1 (K), D37.1 (K), D38.1 (K), D39.1 (K), U2.9 (6/D7)
row3: D19.1 (K), D20.1 (K), D21.1 (K), U1.10 (7/E6)
row3_r: D40.1 (K), D41.1 (K), D42.1 (K), U2.10 (7/E6)

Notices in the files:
PCBs/TheTick_Tick/processed.kicad_pcb:
Copyright (C) 2024, 2025 Jakub \"lenwe\" Kramarz
CERN Open Hardware Licence Version 2 - Strongly Reciprocal
PCBs/Tiny4FSK_Tiny4FSK/processed.kicad_pcb:
Licensed under CERN-OHL-W-2.0
